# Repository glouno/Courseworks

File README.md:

# Courseworks
Different Courseworks from my BEng at KCL

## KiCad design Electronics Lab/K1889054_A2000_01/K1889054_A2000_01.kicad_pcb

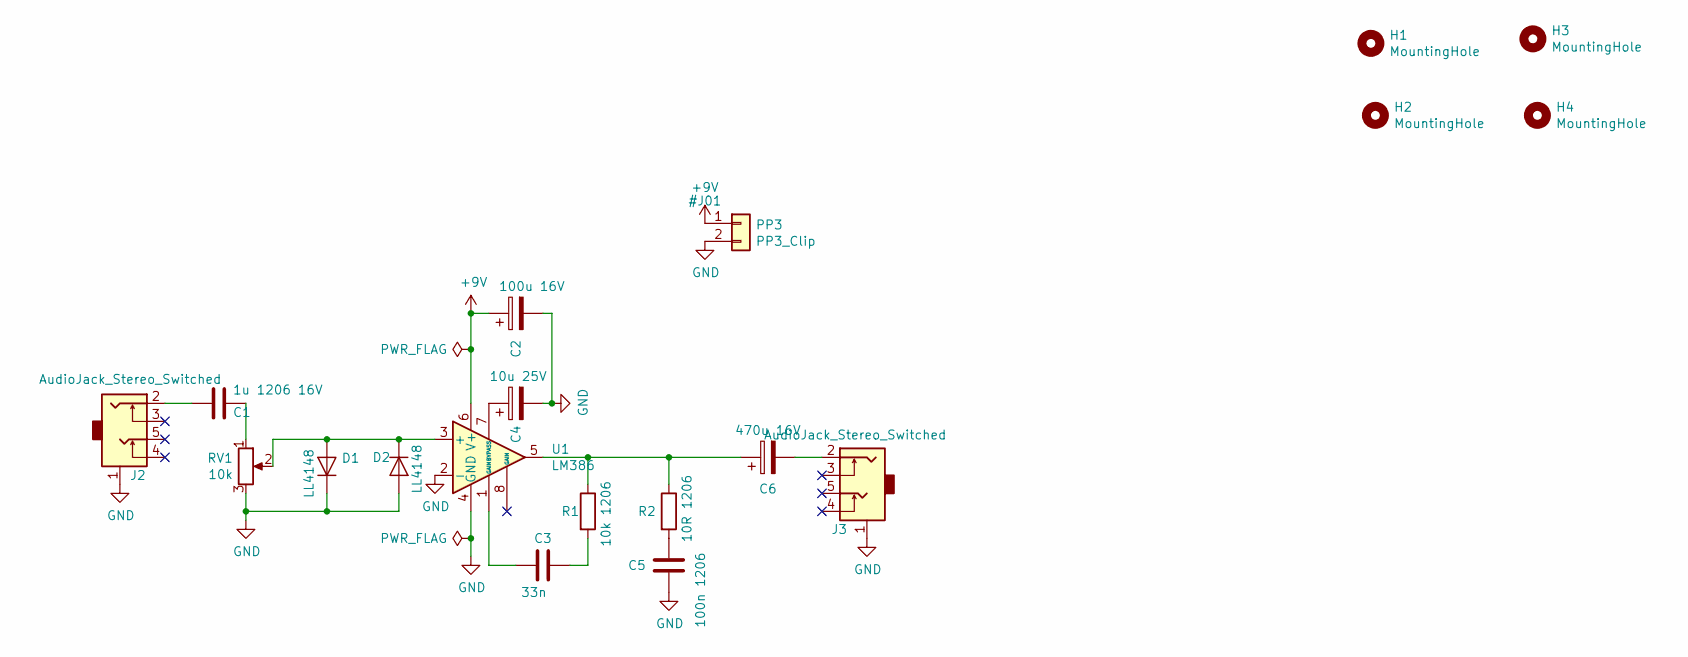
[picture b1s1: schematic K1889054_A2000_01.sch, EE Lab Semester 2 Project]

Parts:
C1: 1u 1206 16V; C_1206_3216Metric
C2: 100u 16V; CP_Radial_D5.0mm_P2.00mm
C3: 33n; C_1206_3216Metric
C4: 10u 25V; CP_Radial_D5.0mm_P2.00mm
C5: 100n 1206; C_1206_3216Metric
C6: 470u 16V; CP_Radial_D8.0mm_P3.50mm
D1, D2: LL4148; D_MiniMELF
H1, H2, H3, H4: MountingHole; MountingHole_3.2mm_M3
J2, J3: AudioJack_Stereo_Switched; StereoJack_3.5mm_Switched
PP3: PP3_Clip; PP3
R1: 10k 1206; R_1206_3216Metric
R2: 10R 1206; R_1206_3216Metric
RV1: 10k; Potentiometer_3386F_Vertical
U1: LM386; SOIC-8_3.9x4.9mm_P1.27mm

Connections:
+9V: C2.1, PP3.1, U1.6 (V+)
GND: C2.2, C4.2, C5.1, D1.1 (K), D2.2 (A), J2.1, J3.1, PP3.2, RV1.3, U1.2 (-), U1.4 (GND)
unnamed: C1.1, RV1.1
unnamed: C1.2, J2.2
unnamed: C3.1, R1.2
unnamed: C3.2, U1.1 (GAIN)
unnamed: C4.1, U1.7 (BYPASS)
unnamed: C5.2, R2.2
unnamed: C6.1, R1.1, R2.1, U1.5
unnamed: C6.2, J3.2
unnamed: D1.2 (A), D2.1 (K), RV1.2, U1.3 (+)

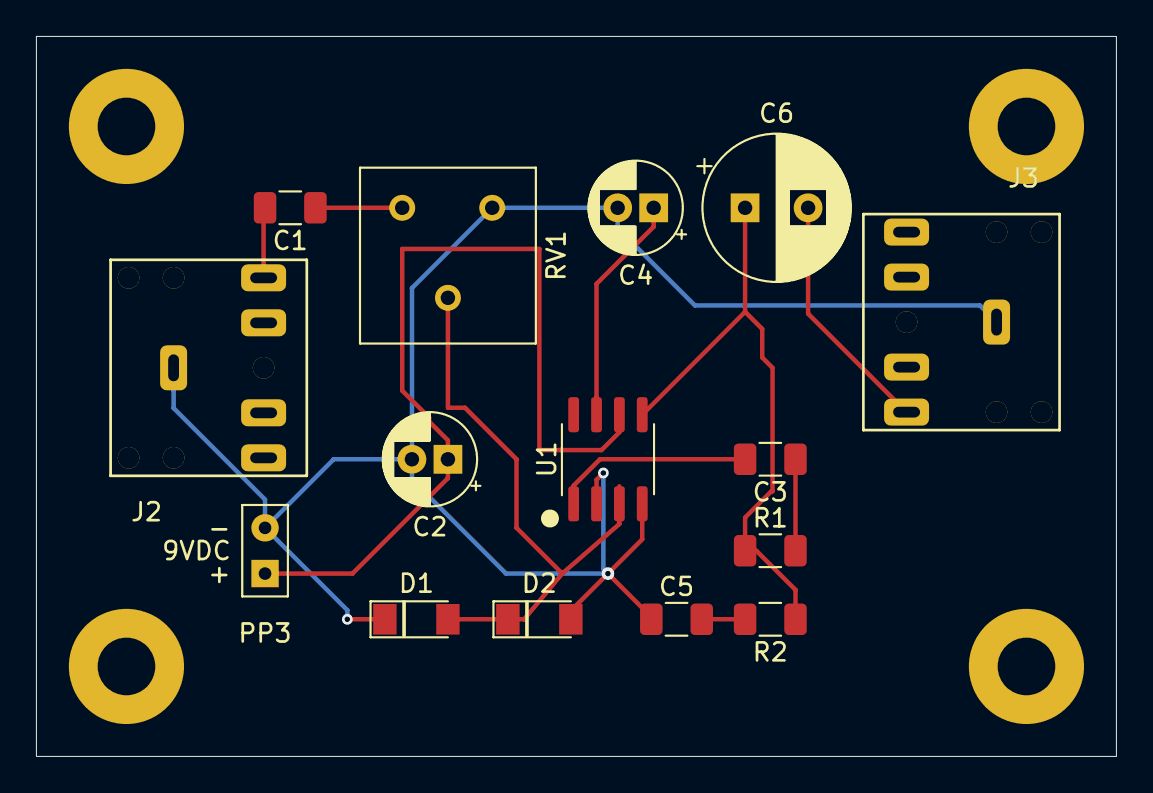
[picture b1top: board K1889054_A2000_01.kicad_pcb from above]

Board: 2 copper layers, 60.0 x 40.0 mm, 19 parts (0 on the bottom side), 11 nets.

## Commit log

2021-07-30 Add project1 files test
2021-07-30 Revert "Add project1 files test"
    This reverts commit d199418d3515147df20b18e22083936b71bc2766.
2021-07-30 HAD file upload
2021-07-30 RTS and COV files
2021-07-30 VER file upload
    language: GCLang compiler in xCheck software
2021-07-30 Electronics Lab files
    PCB design, gerber files
2021-07-30 PRP Programming Practice files
    Python code, a bunch of exercises and 2 courseworks
2021-07-30 CS1 Computer Systems files
    assembly language (run on arduino)
